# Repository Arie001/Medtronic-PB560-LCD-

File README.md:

# Medtronic PB560 LCD 
 Hardware Design for PB560

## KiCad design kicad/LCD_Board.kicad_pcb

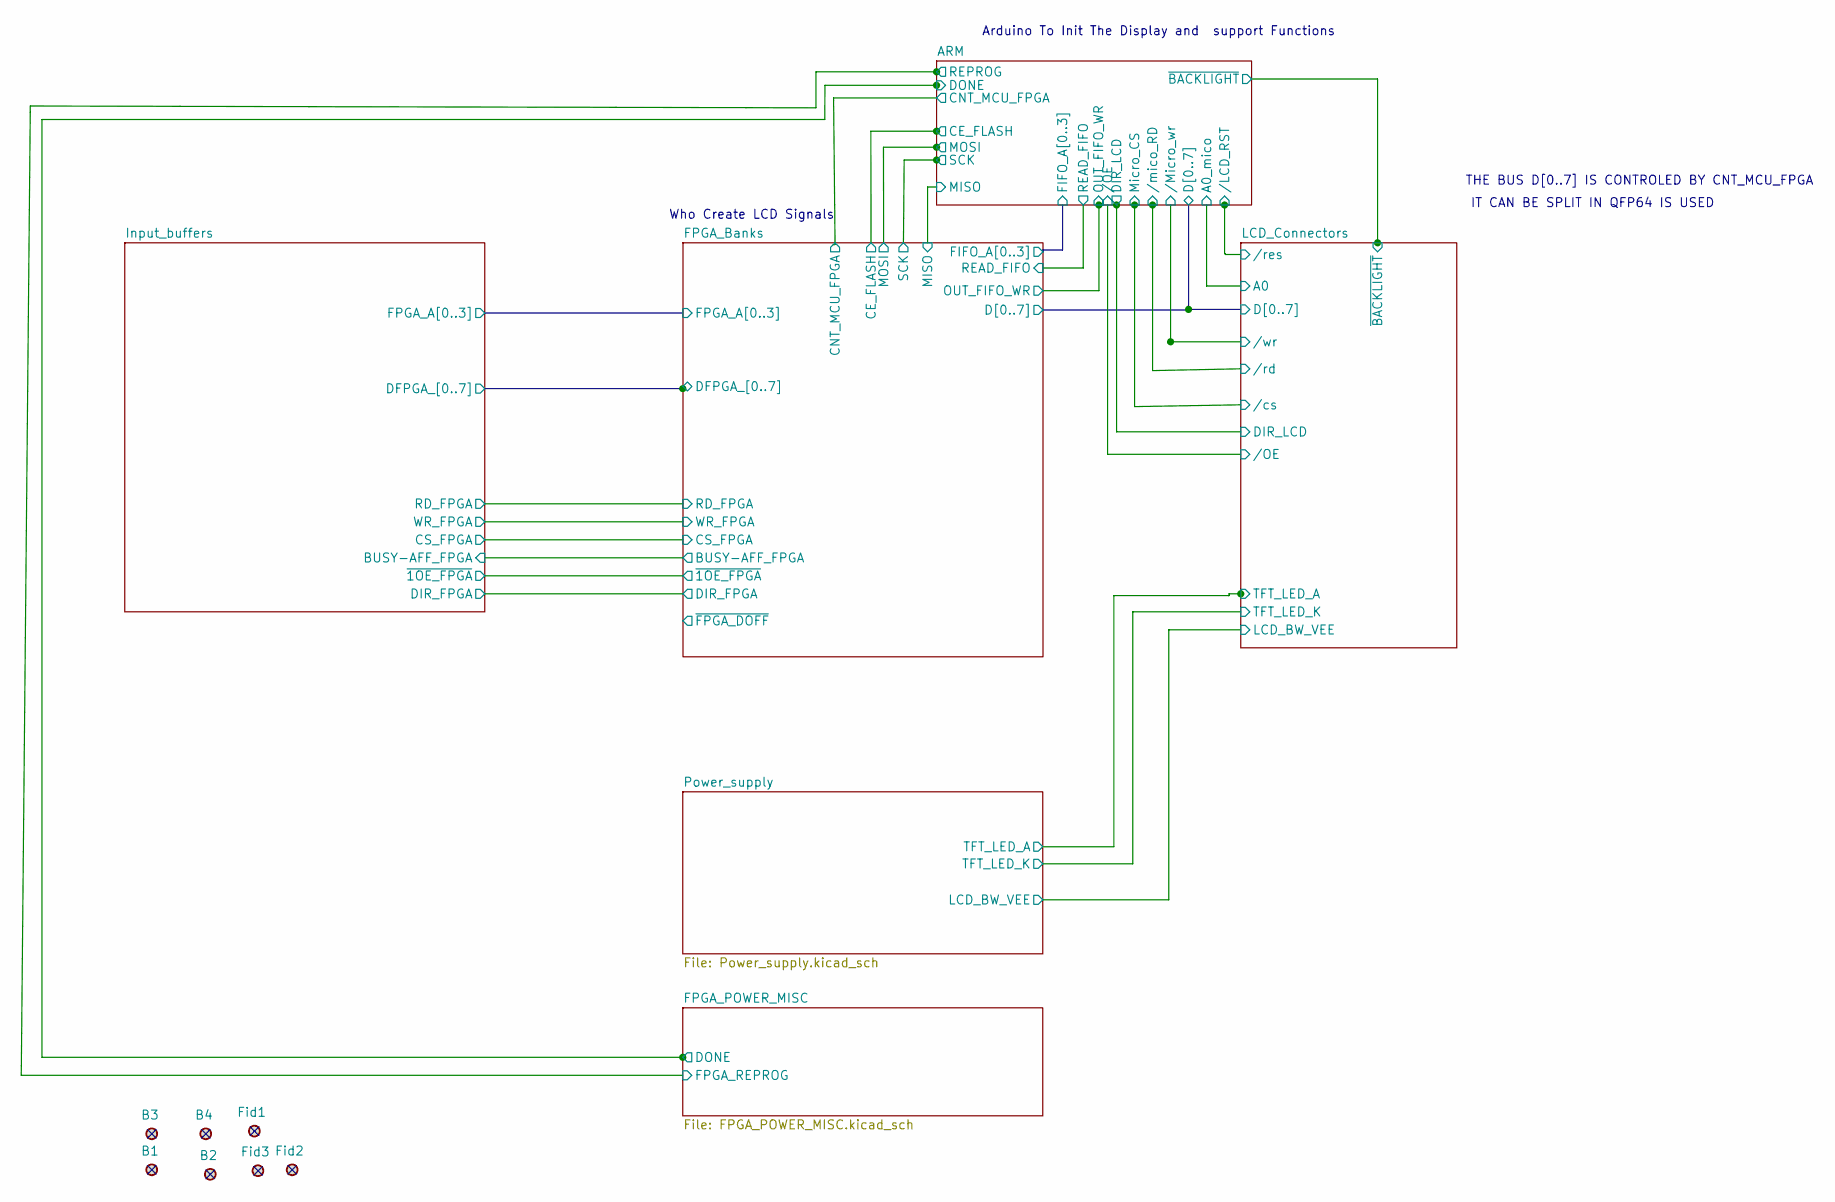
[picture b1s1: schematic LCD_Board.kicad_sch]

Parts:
B1, B2, B3, B4: PLATED_HOLE3.5_PAD6.5; MTG350_650; Part Number PLATED_HOLE3.5_PAD6.5
Fid1, Fid2, Fid3: PLATED_HOLE3.5_PAD6.5-Pads; Fiducial_1mm_Mask2mm; Part Number PLATED_HOLE3.5_PAD6.5

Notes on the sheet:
Who Create LCD Signals
Arduino To Init The Display and support Functions
IT CAN BE SPLIT IN QFP64 IS USED
THE BUS D[0..7] IS CONTROLED BY CNT_MCU_FPGA

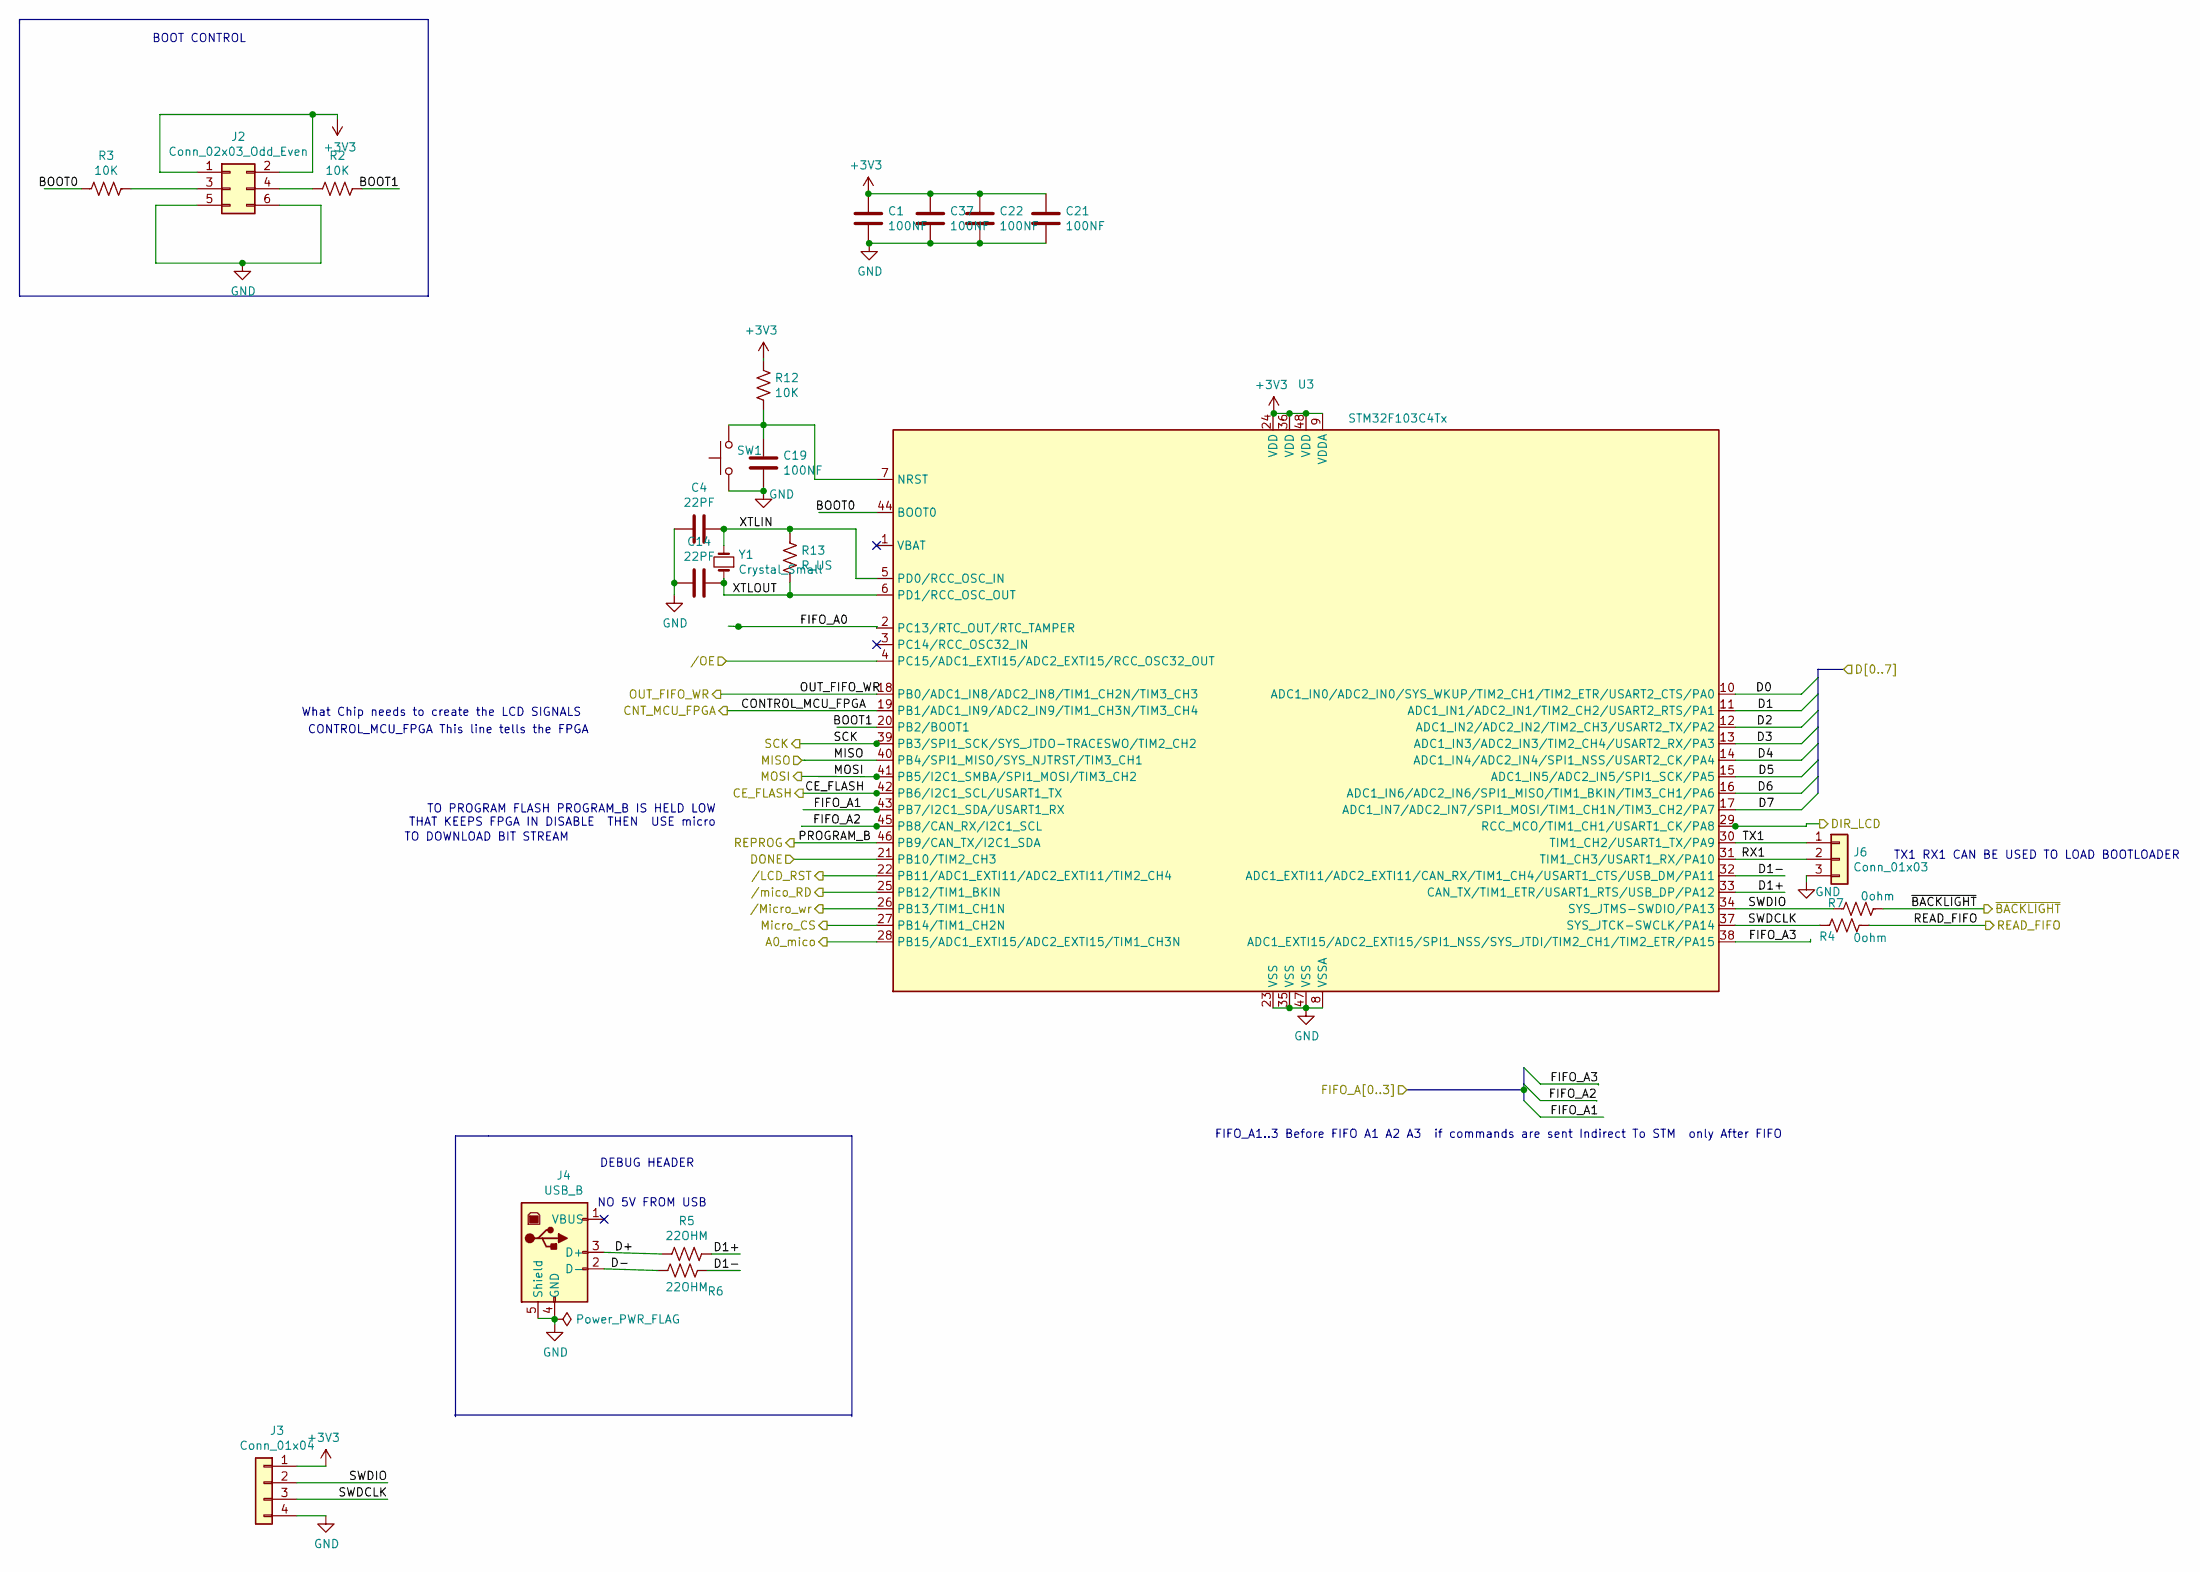
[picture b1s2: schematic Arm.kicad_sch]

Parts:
C1, C19, C21, C22, C37: 100NF; C_0603_1608Metric_Pad0.99x1.00mm_HandSolder
C4, C14: 22PF; C_0603_1608Metric_Pad0.99x1.00mm_HandSolder
J2: Conn_02x03_Odd_Even; PinHeader_2x03_P2.54mm_Horizontal
J3: Conn_01x04; PinHeader_1x04_P2.54mm_Horizontal
J4: USB_B; USB_Micro-B_Wuerth_629105150521
J6: Conn_01x03; PinHeader_1x03_P2.54mm_Vertical
R2, R3, R12: 10K; R_0603_1608Metric_Pad0.99x1.00mm_HandSolder
R4, R7: 0ohm; R_0603_1608Metric_Pad0.99x1.00mm_HandSolder
R5, R6: 22OHM; R_0603_1608Metric_Pad0.99x1.00mm_HandSolder
R13: R_US; R_0603_1608Metric_Pad0.99x1.00mm_HandSolder
SW1: SW_Push; PinHeader_1x02_P2.54mm_Vertical
U3: STM32F103C4Tx; TQFP-48-1EP_7x7mm_P0.5mm_EP5x5mm; lcsc C8734
Y1: Crystal_Small; Crystal_SMD_HC49-SD

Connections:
+3V3: C1.1, C21.1, C22.1, C37.1, J2.1, J2.2, J3.1, R12.1, U3.9 (VDDA), U3.24 (VDD), U3.36 (VDD), U3.48 (VDD); also elsewhere on the board
/A0_mico: U3.28 (PB15/ADC1_EXTI15/ADC2_EXTI15/TIM1_CH3N); also elsewhere on the board
/ARM/BOOT0: R3.1, U3.44 (BOOT0)
/ARM/BOOT1: R2.2, U3.20 (PB2/BOOT1)
/ARM/D1+: R5.2, U3.33 (CAN_TX/TIM1_ETR/USART1_RTS/USB_DP/PA12)
/ARM/D1-: R6.2, U3.32 (ADC1_EXTI11/ADC2_EXTI11/CAN_RX/TIM1_CH4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)
/ARM/RX1: J6.2, U3.31 (TIM1_CH3/USART1_RX/PA10)
/ARM/SWDCLK: J3.3, R4.2, U3.37 (SYS_JTCK-SWCLK/PA14)
/ARM/SWDIO: J3.2, R7.2, U3.34 (SYS_JTMS-SWDIO/PA13)
/ARM/TX1: J6.1, U3.30 (TIM1_CH2/USART1_TX/PA9)
/ARM/XTLIN: C4.1, R13.1, U3.5 (PD0/RCC_OSC_IN), Y1.2
/ARM/XTLOUT: C14.2, R13.2, U3.6 (PD1/RCC_OSC_OUT), Y1.1
/CE_FLASH: U3.42 (PB6/I2C1_SCL/USART1_TX); also elsewhere on the board
/CNT_MCU_FPGA: U3.19 (PB1/ADC1_IN9/ADC2_IN9/TIM1_CH3N/TIM3_CH4); also elsewhere on the board
/D0: U3.10 (ADC1_IN0/ADC2_IN0/SYS_WKUP/TIM2_CH1/TIM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); also elsewhere on the board
/D1: U3.11 (ADC1_IN1/ADC2_IN1/TIM2_CH2/USART2_RTS/P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); also elsewhere on the board
/D2: U3.12 (ADC1_IN2/ADC2_IN2/TIM2_CH3/USART2_TX/PA2); also elsewhere on the board
/D3: U3.13 (ADC1_IN3/ADC2_IN3/TIM2_CH4/USART2_RX/PA3); also elsewhere on the board
/D4: U3.14 (ADC1_IN4/ADC2_IN4/SPI1_NSS/USART2_CK/PA4); also elsewhere on the board
/D5: U3.15 (ADC1_IN5/ADC2_IN5/SPI1_SCK/PA5); also elsewhere on the board
/D6: U3.16 (ADC1_IN6/ADC2_IN6/SPI1_MISO/TIM1_BKIN/T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); also elsewhere on the board
/D7: U3.17 (ADC1_IN7/ADC2_IN7/SPI1_MOSI/TIM1_CH1N/T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); also elsewhere on the board
/DIR_LCD: U3.29 (RCC_MCO/TIM1_CH1/USART1_CK/PA8); also elsewhere on the board
/DONE: U3.21 (PB10/TIM2_CH3); also elsewhere on the board
/FIFO_A0: U3.2 (PC13/RTC_OUT/RTC_TAMPER); also elsewhere on the board
/FIFO_A1: U3.43 (PB7/I2C1_SDA/USART1_RX); also elsewhere on the board
/FIFO_A2: U3.45 (PB8/CAN_RX/I2C1_SCL); also elsewhere on the board
/FIFO_A3: U3.38 (ADC1_EXTI15/ADC2_EXTI15/SPI1_NSS/SYS_JT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); also elsewhere on the board
/MISO: U3.40 (PB4/SPI1_MISO/SYS_NJTRST/TIM3_CH1); also elsewhere on the board
/MOSI: U3.41 (PB5/I2C1_SMBA/SPI1_MOSI/TIM3_CH2); also elsewhere on the board
/Micro_CS: U3.27 (PB14/TIM1_CH2N); also elsewhere on the board
/OUT_FIFO_WR: U3.18 (PB0/ADC1_IN8/ADC2_IN8/TIM1_CH2N/TIM3_CH3); also elsewhere on the board
/READ_FIFO: R4.1; also elsewhere on the board
/REPROG: U3.46 (PB9/CAN_TX/I2C1_SDA); also elsewhere on the board
/SCK: U3.39 (PB3/SPI1_SCK/SYS_JTDO-TRACESWO/TIM2_CH2); also elsewhere on the board
//LCD_RST: U3.22 (PB11/ADC1_EXTI11/ADC2_EXTI11/TIM2_CH4); also elsewhere on the board
//Micro_wr: U3.26 (PB13/TIM1_CH1N); also elsewhere on the board
//OE: U3.4 (PC15/ADC1_EXTI15/ADC2_EXTI15/RCC_OSC32_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); also elsewhere on the board
//mico_RD: U3.25 (PB12/TIM1_BKIN); also elsewhere on the board
/~BACKLIGHT~: R7.1; also elsewhere on the board
GND: C1.2, C4.2, C14.1, C19.2, C21.2, C22.2, C37.2, J2.5, J2.6, J3.4, J4.4 (GND), J4.5 (Shield), J6.3, SW1.1, U3.8 (VSSA), U3.23 (VSS), U3.35 (VSS), U3.47 (VSS); also elsewhere on the board
unnamed: C19.1, R12.2, SW1.2, U3.7 (NRST)
unnamed: J2.3, R3.2
unnamed: J2.4, R2.1
unnamed: J4.2 (D-), R6.1
unnamed: J4.3 (D+), R5.1

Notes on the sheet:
BOOT CONTROL
TO DOWNLOAD BIT STREAM
What Chip needs to create the LCD SIGNALS
CONTROL_MCU_FPGA This line tells the FPGA
DEBUG HEADER
NO 5V FROM USB
TO PROGRAM FLASH PROGRAM_B IS HELD LOW THAT KEEPS FPGA IN DISABLE THEN USE micro
FIFO_A1..3 Before FIFO A1 A2 A3 if commands are sent Indirect To STM only After FIFO
TX1 RX1 CAN BE USED TO LOAD BOOTLOADER

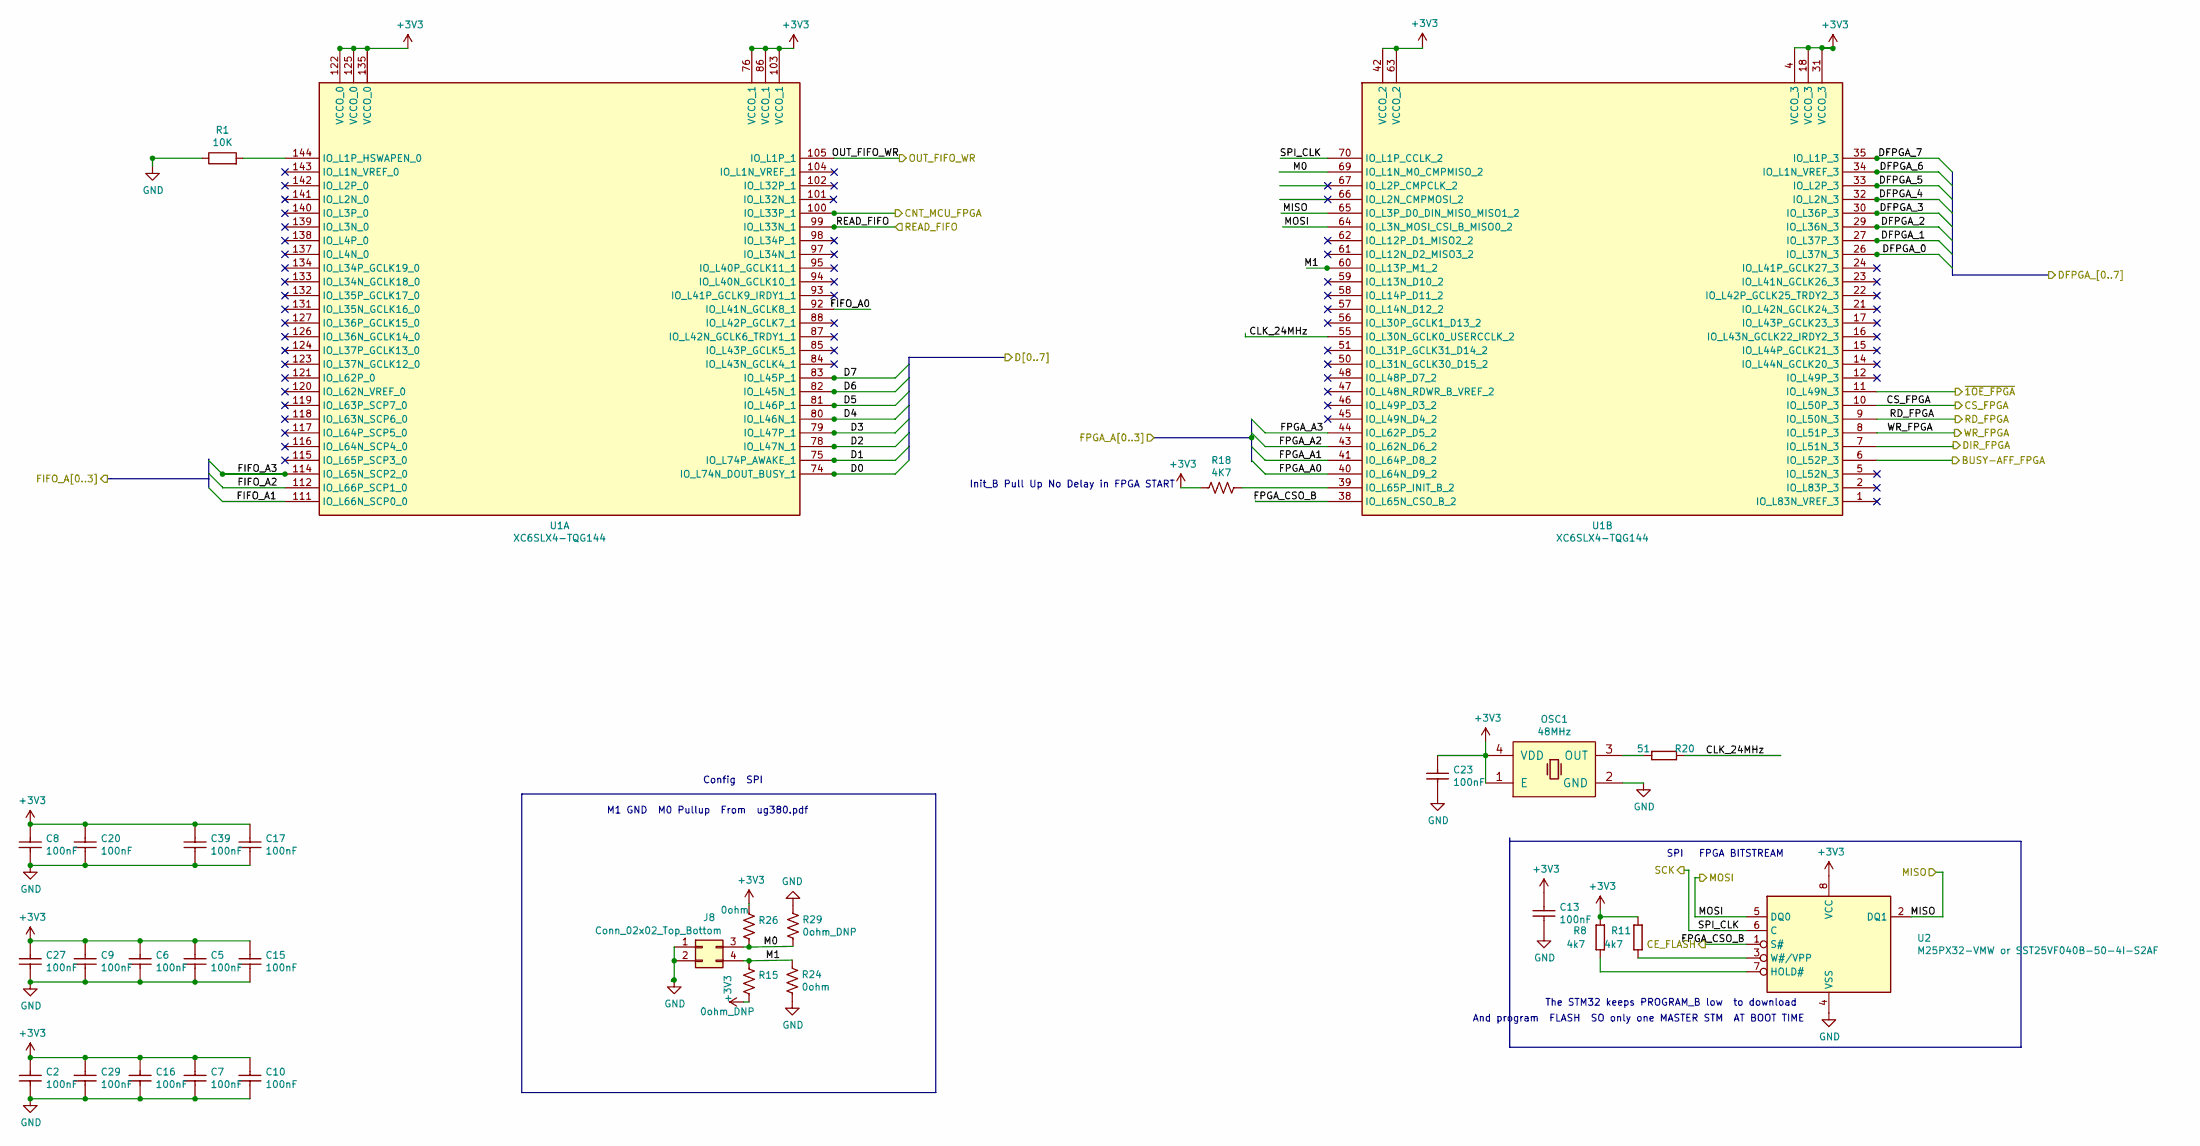
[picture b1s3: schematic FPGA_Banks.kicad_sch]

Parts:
C2, C5, C6, C7, C8, C9, C10, C13, C15, C16, C17, C20, C23, C27, C29, C39: CC0201_100NF_6.3V_10%_X5R; C_0603_1608Metric_Pad0.99x1.00mm_HandSolder; Voltage 6.3V; Tolerance ±10%; Part Number CC0201_100NF_6.3V_10%_X5R
J8: Conn_02x02_Top_Bottom; PinHeader_2x02_P2.54mm_Vertical
OSC1: OSC_48MHZ_TXC_7C-48.000MBA-T; OSC_TXC_7C; Part Number OSC_48MHZ_TXC_7C-48.000MBA-T; lcsc C32533
R1: 10K; R_0603_1608Metric_Pad0.99x1.00mm_HandSolder
R8: R0402_4K7_1%_0.0625W_100PPM; R_0603_1608Metric_Pad0.99x1.00mm_HandSolder; Part Number R0402_4K7_1%_0.0625W_100PPM
R11: R0402_4K7_1%_0.0625W_100PPM; R_0603_1608Metric_Pad0.99x1.00mm_HandSolder; Tolerance ±1%; Part Number R0402_4K7_1%_0.0625W_100PPM
R15, R29: 0ohm_DNP; R_0603_1608Metric_Pad0.99x1.00mm_HandSolder
R18: 4K7; R_0603_1608Metric_Pad0.99x1.00mm_HandSolder
R20: R0402_51R_1%_0.0625W_100PPM; R_0603_1608Metric_Pad0.99x1.00mm_HandSolder; Tolerance ±1%; Part Number R0402_51R_1%_0.0625W_100PPM
R24, R26: 0ohm; R_0603_1608Metric_Pad0.99x1.00mm_HandSolder
U1: XC6SLX4-TQG144; LQFP-144_20x20mm_P0.5mm; Manufacturer Part Number XC6SLX4-TQG144; lcsc C169796
U2: M25PX32-VMW or SST25VF040B-50-4I-S2AF; SO-8_3.9x4.9mm_P1.27mm; Manufacturer Part Number SST25VF040B-50-4I-S2AF; lcsc C178274

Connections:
+3V3: C2.1, C5.1, C6.1, C7.1, C8.1, C9.1, C10.1, C13.1, C15.1, C16.1, C17.1, C20.1, C23.1, C27.1, C29.1, C39.1, OSC1.1 (E), OSC1.4 (VDD), R8.1, R11.1, R15.2, R18.1, R26.1, U1.4 (VCCO_3), U1.18 (VCCO_3), U1.31 (VCCO_3), U1.42 (VCCO_2), U1.63 (VCCO_2), U1.76 (VCCO_1), U1.86 (VCCO_1), U1.103 (VCCO_1), U1.122 (VCCO_0), U1.125 (VCCO_0), U1.135 (VCCO_0), U2.8 (VCC); also elsewhere on the board
/BUSY-AFF_FPGA: U1.6 (IO_L52P_3); also elsewhere on the board
/CE_FLASH: U1.38 (IO_L65N_CSO_B_2), U2.1 (S#); also elsewhere on the board
/CNT_MCU_FPGA: U1.100 (IO_L33P_1); also elsewhere on the board
/CS_FPGA: U1.10 (IO_L50P_3); also elsewhere on the board
/D0: U1.74 (IO_L74N_DOUT_BUSY_1); also elsewhere on the board
/D1: U1.75 (IO_L74P_AWAKE_1); also elsewhere on the board
/D2: U1.78 (IO_L47N_1); also elsewhere on the board
/D3: U1.79 (IO_L47P_1); also elsewhere on the board
/D4: U1.80 (IO_L46N_1); also elsewhere on the board
/D5: U1.81 (IO_L46P_1); also elsewhere on the board
/D6: U1.82 (IO_L45N_1); also elsewhere on the board
/D7: U1.83 (IO_L45P_1); also elsewhere on the board
/DFPGA_0: U1.26 (IO_L37N_3); also elsewhere on the board
/DFPGA_1: U1.27 (IO_L37P_3); also elsewhere on the board
/DFPGA_2: U1.29 (IO_L36N_3); also elsewhere on the board
/DFPGA_3: U1.30 (IO_L36P_3); also elsewhere on the board
/DFPGA_4: U1.32 (IO_L2N_3); also elsewhere on the board
/DFPGA_5: U1.33 (IO_L2P_3); also elsewhere on the board
/DFPGA_6: U1.34 (IO_L1N_VREF_3); also elsewhere on the board
/DFPGA_7: U1.35 (IO_L1P_3); also elsewhere on the board
/DIR_FPGA: U1.7 (IO_L51N_3); also elsewhere on the board
/FIFO_A0: U1.92 (IO_L41N_GCLK8_1); also elsewhere on the board
/FIFO_A1: U1.111 (IO_L66N_SCP0_0); also elsewhere on the board
/FIFO_A2: U1.112 (IO_L66P_SCP1_0); also elsewhere on the board
/FIFO_A3: U1.114 (IO_L65N_SCP2_0); also elsewhere on the board
/FPGA_A0: U1.40 (IO_L64N_D9_2); also elsewhere on the board
/FPGA_A1: U1.41 (IO_L64P_D8_2); also elsewhere on the board
/FPGA_A2: U1.43 (IO_L62N_D6_2); also elsewhere on the board
/FPGA_A3: U1.44 (IO_L62P_D5_2); also elsewhere on the board
/FPGA_Banks/CLK_24MHz: R20.2, U1.55 (IO_L30N_GCLK0_USERCCLK_2)
/FPGA_Banks/M0: J8.3, R26.2, R29.2, U1.69 (IO_L1N_M0_CMPMISO_2)
/FPGA_Banks/M1: J8.4, R15.1, R24.1, U1.60 (IO_L13P_M1_2)
/MISO: U1.65 (IO_L3P_D0_DIN_MISO_MISO1_2), U2.2 (DQ1); also elsewhere on the board
/MOSI: U1.64 (IO_L3N_MOSI_CSI_B_MISO0_2), U2.5 (DQ0); also elsewhere on the board
/OUT_FIFO_WR: U1.105 (IO_L1P_1); also elsewhere on the board
/RD_FPGA: U1.9 (IO_L50N_3); also elsewhere on the board
/READ_FIFO: U1.99 (IO_L33N_1); also elsewhere on the board
/SCK: U1.70 (IO_L1P_CCLK_2), U2.6 (C); also elsewhere on the board
/WR_FPGA: U1.8 (IO_L51P_3); also elsewhere on the board
/~1OE_FPGA~: U1.11 (IO_L49N_3); also elsewhere on the board
GND: C2.2, C5.2, C6.2, C7.2, C8.2, C9.2, C10.2, C13.2, C15.2, C16.2, C17.2, C20.2, C23.2, C27.2, C29.2, C39.2, J8.1, J8.2, OSC1.2 (GND), R1.1, R24.2, R29.1, U2.4 (VSS); also elsewhere on the board
unnamed: OSC1.3 (OUT), R20.1
unnamed: R1.2, U1.144 (IO_L1P_HSWAPEN_0)
unnamed: R8.2, U2.7 (HOLD#)
unnamed: R11.2, U2.3 (W#/VPP)
unnamed: R18.2, U1.39 (IO_L65P_INIT_B_2)

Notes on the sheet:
Config SPI
M1 GND M0 Pullup From ug380.pdf
Init_B Pull Up No Delay in FPGA START
SPI FPGA BITSTREAM
The STM32 keeps PROGRAM_B low to download
And program FLASH SO only one MASTER STM AT BOOT TIME

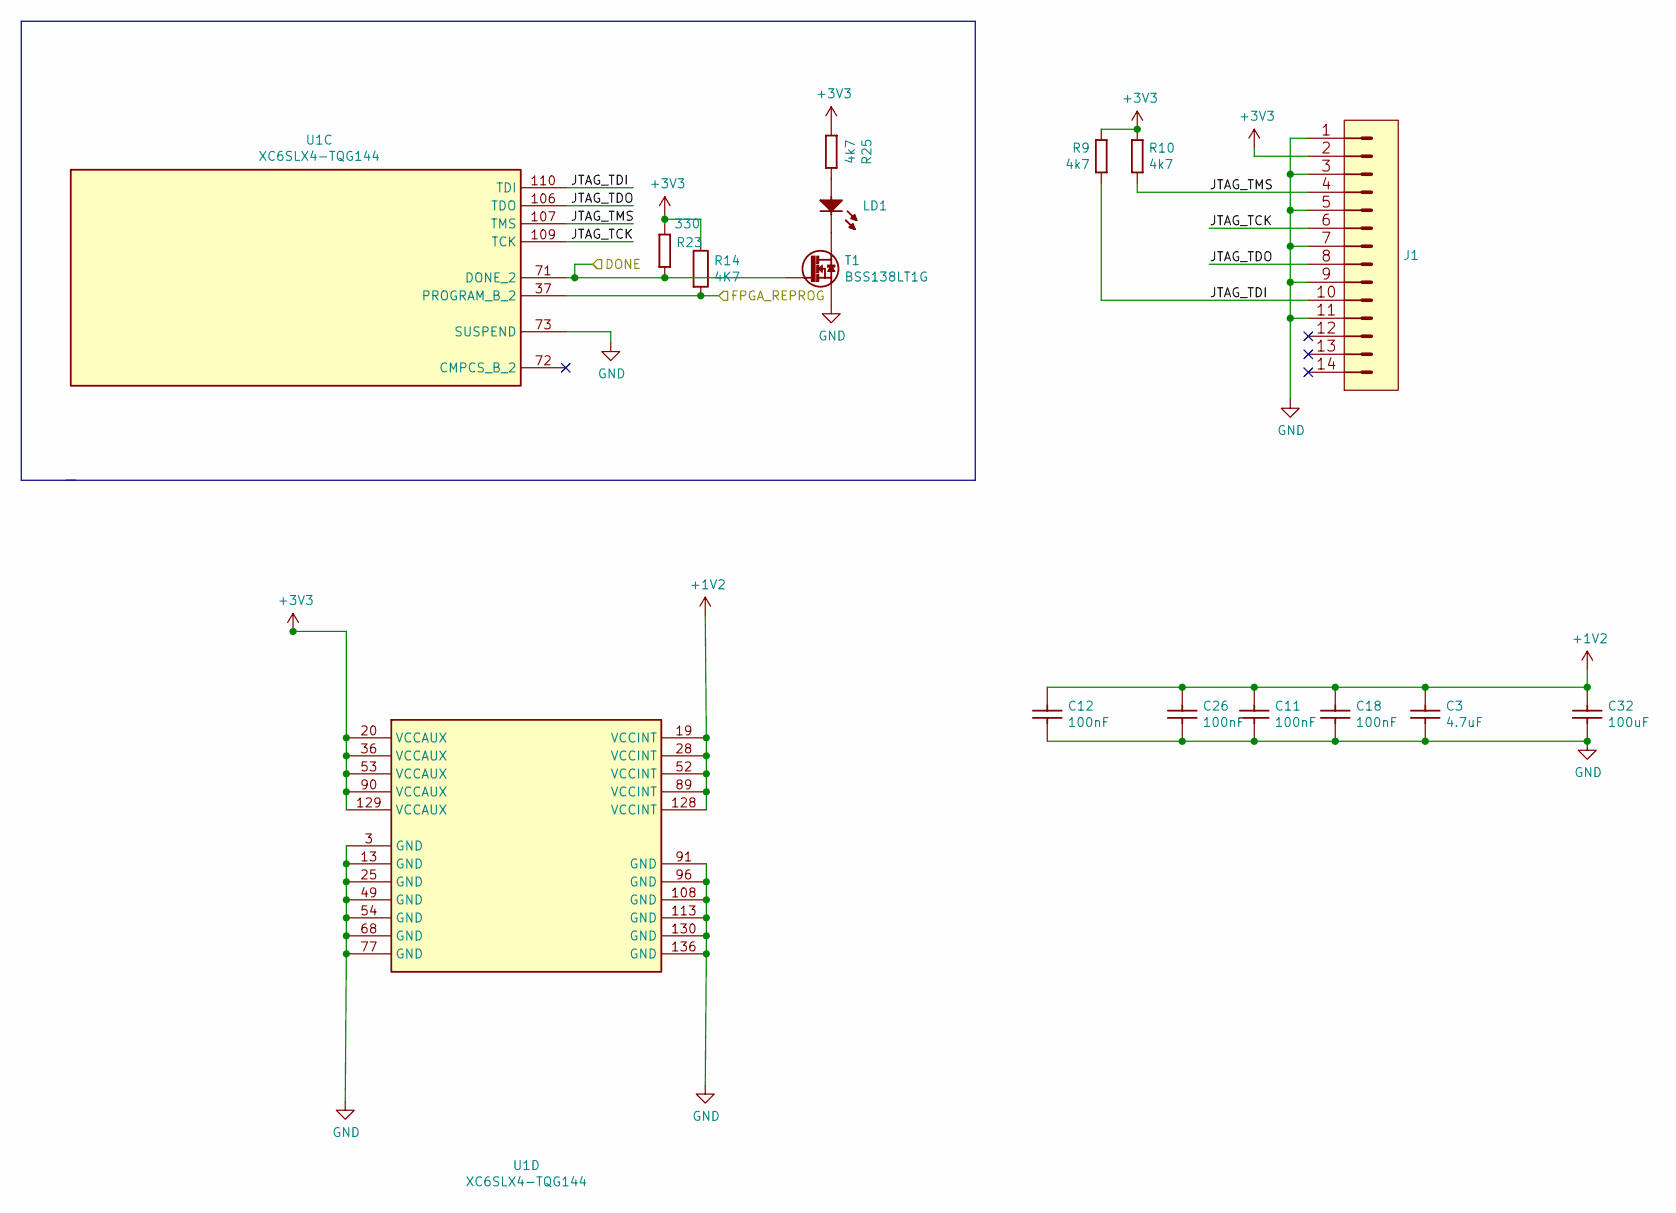
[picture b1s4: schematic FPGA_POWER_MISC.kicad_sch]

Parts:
C3: CC0402_4.7UF_6.3V_20%_X5R; C_0603_1608Metric_Pad0.99x1.00mm_HandSolder; Voltage 6.3V; Tolerance ±20%; Part Number CC0402_4.7UF_6.3V_20%_X5R
C11, C12, C18, C26: CC0201_100NF_6.3V_10%_X5R; C_0603_1608Metric_Pad0.99x1.00mm_HandSolder; Voltage 6.3V; Tolerance ±10%; Part Number CC0201_100NF_6.3V_10%_X5R
C32: CC1206_100UF_6.3V_20%_X5R; C_0603_1608Metric_Pad0.99x1.00mm_HandSolder; Voltage 6.3V; Tolerance ±10%; Part Number CC1206_100UF_6.3V_20%_X5R
J1: MOLEX_87833-1420-MOLEX; MOLEX_87833-1420; Part Number MOLEX_87833-1420
LD1: LED_KINGBRIGHT_KPH-1608CGCK; LED_0603_1608Metric; Part Number LED_KINGBRIGHT_KPH-1608CGCK
R9, R10, R25: R0402_4K7_1%_0.0625W_100PPM; R_0603_1608Metric_Pad0.99x1.00mm_HandSolder; Tolerance ±1%; Part Number R0402_4K7_1%_0.0625W_100PPM
R14: 4K7; R_0603_1608Metric_Pad0.99x1.00mm_HandSolder
R23: R0402_330R_1%_0.0625W_100PPM; R_0603_1608Metric_Pad0.99x1.00mm_HandSolder; Tolerance ±1%; Part Number R0402_330R_1%_0.0625W_100PPM
T1: BSS138LT1G; SOT-23_Handsoldering; Part Number BSS138LT1G; lcsc C8490
U1: XC6SLX4-TQG144; LQFP-144_20x20mm_P0.5mm; Manufacturer Part Number XC6SLX4-TQG144; lcsc C169796

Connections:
+1V2: C3.1, C11.1, C12.1, C18.1, C26.1, C32.1, U1.19 (VCCINT), U1.28 (VCCINT), U1.52 (VCCINT), U1.89 (VCCINT), U1.128 (VCCINT); also elsewhere on the board
+3V3: J1.2, R9.1, R10.1, R14.1, R23.1, R25.1, U1.20 (VCCAUX), U1.36 (VCCAUX), U1.53 (VCCAUX), U1.90 (VCCAUX), U1.129 (VCCAUX); also elsewhere on the board
/DONE: R23.2, T1.1 (G), U1.71 (DONE_2); also elsewhere on the board
/FPGA_POWER_MISC/JTAG_TCK: J1.6, U1.109 (TCK)
/FPGA_POWER_MISC/JTAG_TDI: J1.10, R9.2, U1.110 (TDI)
/FPGA_POWER_MISC/JTAG_TDO: J1.8, U1.106 (TDO)
/FPGA_POWER_MISC/JTAG_TMS: J1.4, R10.2, U1.107 (TMS)
/REPROG: R14.2, U1.37 (PROGRAM_B_2); also elsewhere on the board
GND: C3.2, C11.2, C12.2, C18.2, C26.2, C32.2, J1.1, J1.3, J1.5, J1.7, J1.9, J1.11, T1.2 (S), U1.3 (GND), U1.13 (GND), U1.25 (GND), U1.49 (GND), U1.54 (GND), U1.68 (GND), U1.73 (SUSPEND), U1.77 (GND), U1.91 (GND), U1.96 (GND), U1.108 (GND), U1.113 (GND), U1.130 (GND), U1.136 (GND); also elsewhere on the board
unnamed: LD1.1 (C), T1.3 (D)
unnamed: LD1.2 (A), R25.2

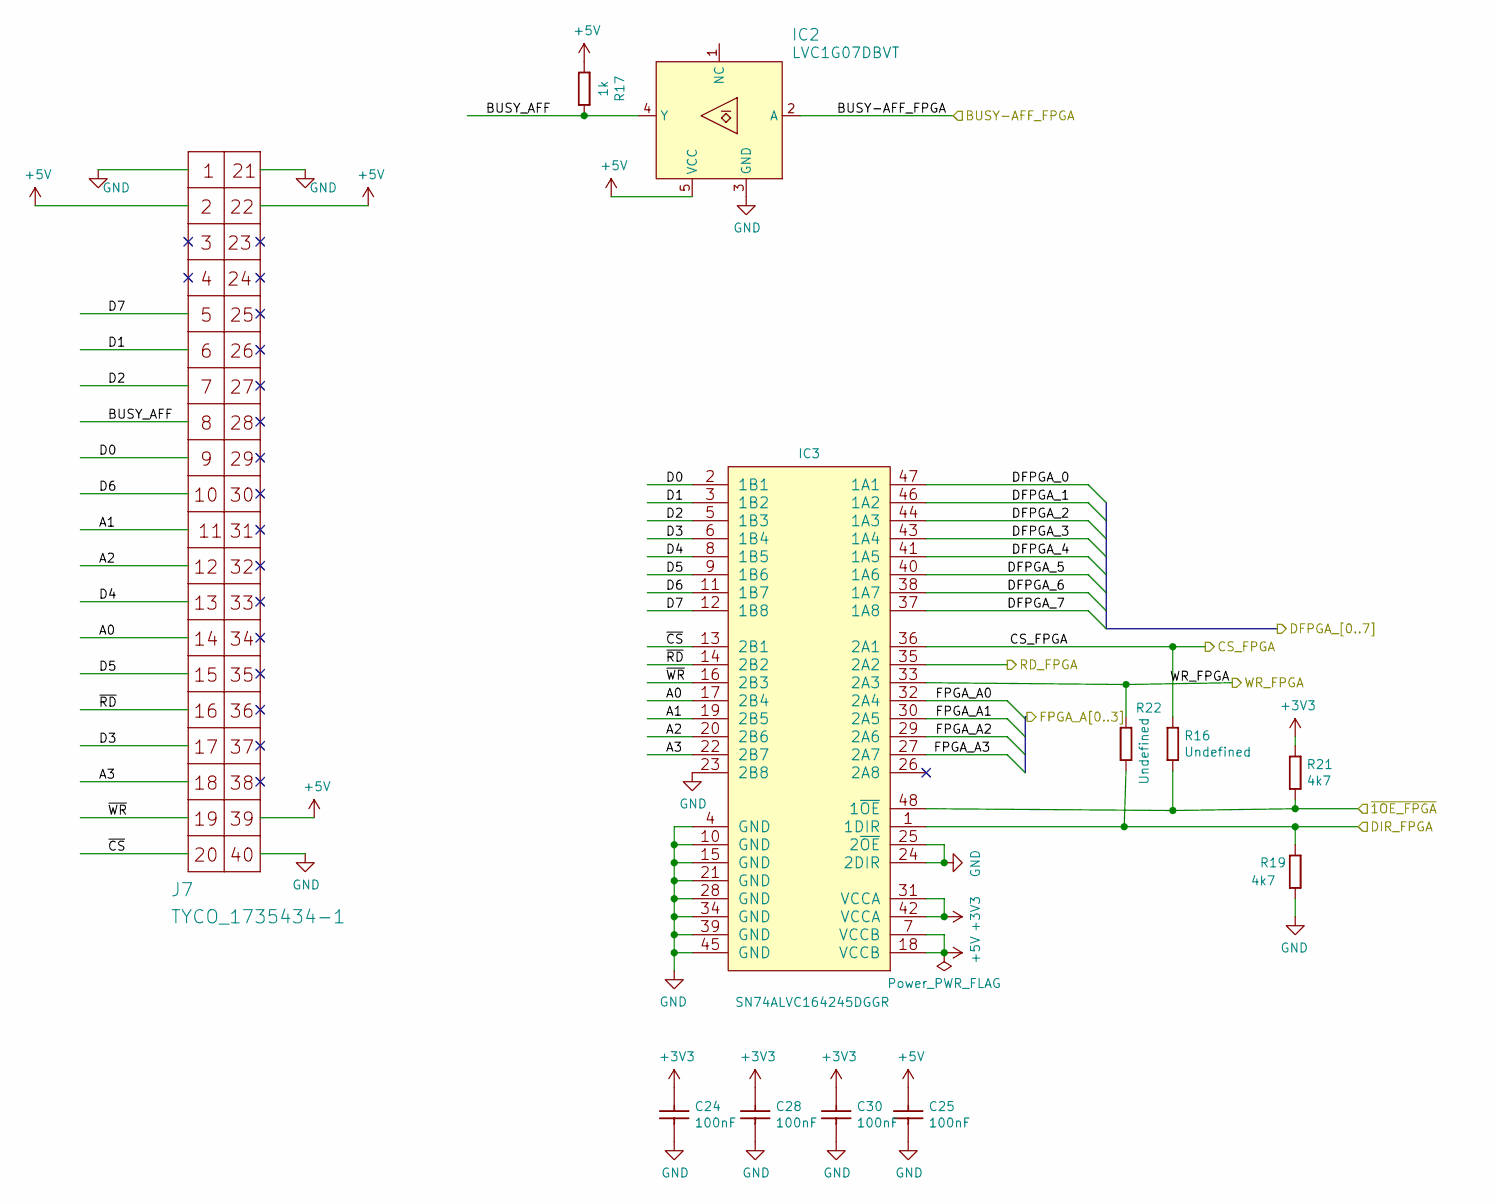
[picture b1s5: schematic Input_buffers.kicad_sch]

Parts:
C24, C25, C28, C30: CC0201_100NF_6.3V_10%_X5R; C_0603_1608Metric_Pad0.99x1.00mm_HandSolder; Voltage 6.3V; Tolerance ±10%; Part Number CC0201_100NF_6.3V_10%_X5R
IC2: LVC1G07DBVT; SC70-5
IC3: SN74ALVC164245DGGR; TSSOP-48_6.1x12.5mm_P0.5mm; Part Number SN74ALVC164245DGGR; lcsc C7128
J7: TYCO_1735434-1
R16, R22: R0402_NO-VALUE; R_0603_1608Metric_Pad0.99x1.00mm_HandSolder; Part Number R0402_NO-VALUE
R17: R0402_1K_1%_0.0625W_100PPM; R_0603_1608Metric_Pad0.99x1.00mm_HandSolder; Tolerance ±1%; Part Number R0402_1K_1%_0.0625W_100PPM
R19, R21: R0402_4K7_1%_0.0625W_100PPM; R_0603_1608Metric_Pad0.99x1.00mm_HandSolder; Tolerance ±1%; Part Number R0402_4K7_1%_0.0625W_100PPM

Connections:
+3V3: C24.1, C28.1, C30.1, IC3.31 (VCCA), IC3.42 (VCCA), R21.1; also elsewhere on the board
+5V: C25.1, IC2.5 (VCC), IC3.7 (VCCB), IC3.18 (VCCB), J7.2, J7.22, J7.39, R17.1; also elsewhere on the board
/BUSY-AFF_FPGA: IC2.2 (A); also elsewhere on the board
/CS_FPGA: IC3.36 (2A1), R16.1; also elsewhere on the board
/DFPGA_0: IC3.47 (1A1); also elsewhere on the board
/DFPGA_1: IC3.46 (1A2); also elsewhere on the board
/DFPGA_2: IC3.44 (1A3); also elsewhere on the board
/DFPGA_3: IC3.43 (1A4); also elsewhere on the board
/DFPGA_4: IC3.41 (1A5); also elsewhere on the board
/DFPGA_5: IC3.40 (1A6); also elsewhere on the board
/DFPGA_6: IC3.38 (1A7); also elsewhere on the board
/DFPGA_7: IC3.37 (1A8); also elsewhere on the board
/DIR_FPGA: IC3.1 (1DIR), R19.1, R22.2; also elsewhere on the board
/FPGA_A0: IC3.32 (2A4); also elsewhere on the board
/FPGA_A1: IC3.30 (2A5); also elsewhere on the board
/FPGA_A2: IC3.29 (2A6); also elsewhere on the board
/FPGA_A3: IC3.27 (2A7); also elsewhere on the board
/Input_buffers/A0: IC3.17 (2B4), J7.14
/Input_buffers/A1: IC3.19 (2B5), J7.11
/Input_buffers/A2: IC3.20 (2B6), J7.12
/Input_buffers/A3: IC3.22 (2B7), J7.18
/Input_buffers/BUSY_AFF: IC2.4 (Y), J7.8, R17.2
/Input_buffers/D0: IC3.2 (1B1), J7.9
/Input_buffers/D1: IC3.3 (1B2), J7.6
/Input_buffers/D2: IC3.5 (1B3), J7.7
/Input_buffers/D3: IC3.6 (1B4), J7.17
/Input_buffers/D4: IC3.8 (1B5), J7.13
/Input_buffers/D5: IC3.9 (1B6), J7.15
/Input_buffers/D6: IC3.11 (1B7), J7.10
/Input_buffers/D7: IC3.12 (1B8), J7.5
/Input_buffers/~CS~: IC3.13 (2B1), J7.20
/Input_buffers/~RD~: IC3.14 (2B2), J7.16
/Input_buffers/~WR~: IC3.16 (2B3), J7.19
/RD_FPGA: IC3.35 (2A2); also elsewhere on the board
/WR_FPGA: IC3.33 (2A3), R22.1; also elsewhere on the board
/~1OE_FPGA~: IC3.48 (1~OE), R16.2, R21.2; also elsewhere on the board
GND: C24.2, C25.2, C28.2, C30.2, IC2.3 (GND), IC3.4 (GND), IC3.10 (GND), IC3.15 (GND), IC3.21 (GND), IC3.23 (2B8), IC3.24 (2DIR), IC3.25 (2~OE), IC3.28 (GND), IC3.34 (GND), IC3.39 (GND), IC3.45 (GND), J7.1, J7.21, J7.40, R19.2; also elsewhere on the board

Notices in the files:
parts and their libraries:
License: This work is licensed under the Creative Commons CC-BY-SA 4.0 License. To the extent that circuit schematics that use Licensed Material can be considered to be ‘Adapted Material’, then the copyright holder waives article 3.b of the license with respect to these schematics.
